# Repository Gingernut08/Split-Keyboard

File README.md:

50 Key Compact Keyboard with 2 function layers and wireless capability

CAD Case Assembled

PCB

Schematic repeated for each half

BOM:

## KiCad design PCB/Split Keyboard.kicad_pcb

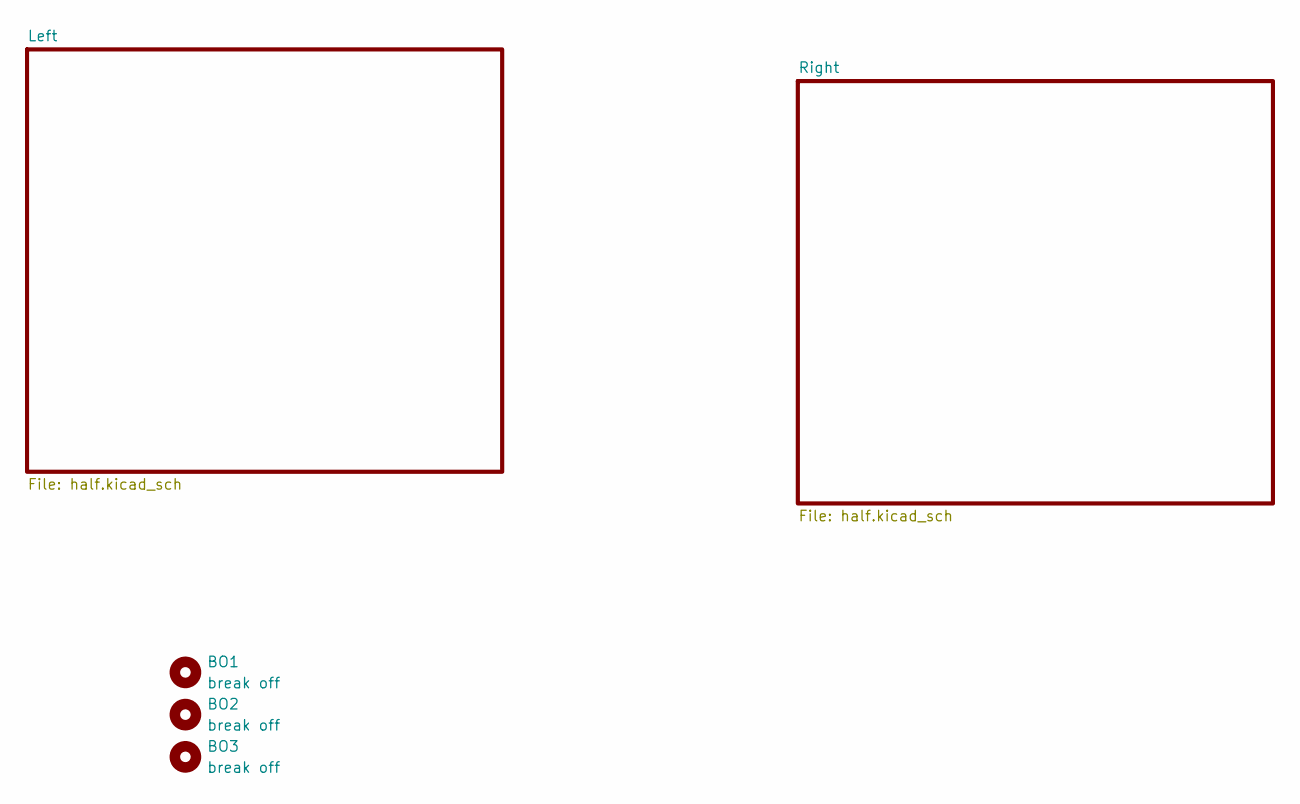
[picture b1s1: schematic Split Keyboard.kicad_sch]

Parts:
BO1, BO2, BO3: break off; mouse-bite-5mm-slot

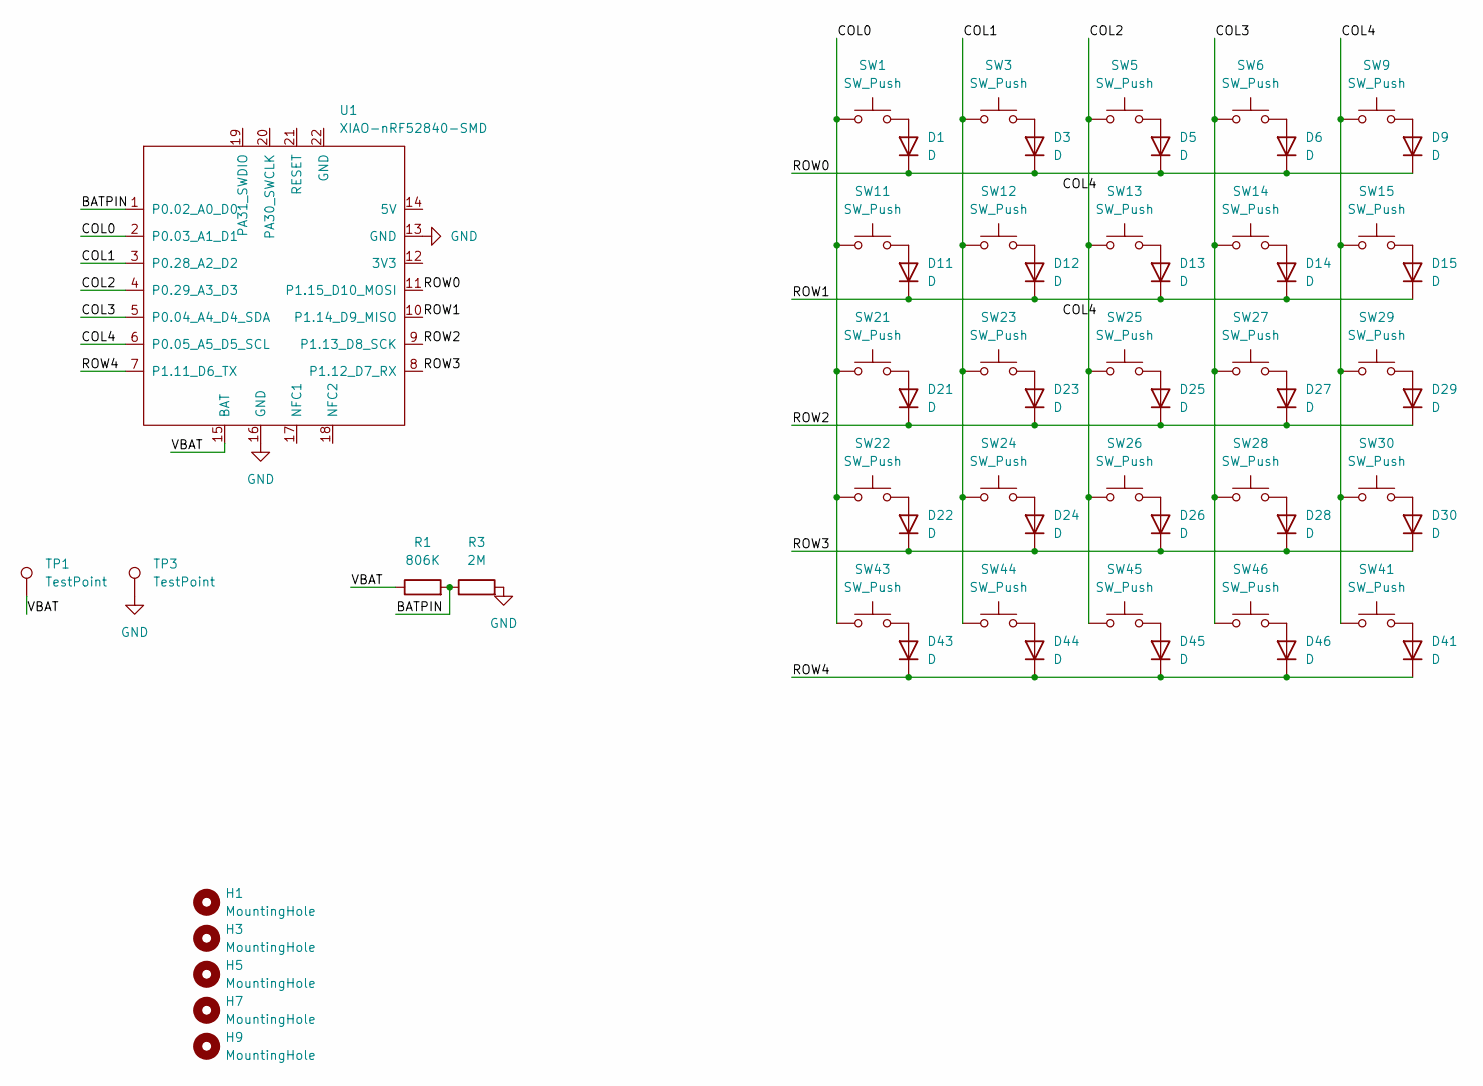
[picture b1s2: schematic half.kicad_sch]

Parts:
D1, D3, D5, D6, D9, D11, D12, D13, D14, D15, D21, D22, D23, D24, D25, D26, D27, D28, D29, D30, D41, D43, D44, D45, D46: D; D_SOD-123
H1, H3, H5, H7, H9: MountingHole; MountingHole_3.2mm_M3
R1: 806K; R_0805_2012Metric
R3: 2M; R_0805_2012Metric
SW1, SW3, SW5, SW6, SW9, SW11, SW12, SW13, SW14, SW15, SW21, SW22, SW23, SW24, SW25, SW26, SW27, SW28, SW29, SW30, SW41, SW43, SW44, SW45, SW46: SW_Push; SW_MX_HS_CPG151101S11_1u
TP1, TP3: TestPoint; TestPoint_Pad_D2.0mm
U1: XIAO-nRF52840-SMD; modified-XIAO-nRF52840-SMD

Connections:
/Right/BATPIN: R1.2, R3.1, U1.1 (P0.02_A0_D0)
/Right/COL0: SW1.1, SW11.1, SW21.1, SW22.1, SW43.1, U1.2 (P0.03_A1_D1)
/Right/COL1: SW3.1, SW12.1, SW23.1, SW24.1, SW44.1, U1.3 (P0.28_A2_D2)
/Right/COL2: SW5.1, SW13.1, SW25.1, SW26.1, SW45.1, U1.4 (P0.29_A3_D3)
/Right/COL3: SW6.1, SW14.1, SW27.1, SW28.1, SW46.1, U1.5 (P0.04_A4_D4_SDA)
/Right/COL4: SW9.1, SW15.1, SW29.1, SW30.1, SW41.1, U1.6 (P0.05_A5_D5_SCL)
/Right/ROW0: D1.1 (K), D3.1 (K), D5.1 (K), D6.1 (K), D9.1 (K), U1.11 (P1.15_D10_MOSI)
/Right/ROW1: D11.1 (K), D12.1 (K), D13.1 (K), D14.1 (K), D15.1 (K), U1.10 (P1.14_D9_MISO)
/Right/ROW2: D21.1 (K), D23.1 (K), D25.1 (K), D27.1 (K), D29.1 (K), U1.9 (P1.13_D8_SCK)
/Right/ROW3: D22.1 (K), D24.1 (K), D26.1 (K), D28.1 (K), D30.1 (K), U1.8 (P1.12_D7_RX)
/Right/ROW4: D41.1 (K), D43.1 (K), D44.1 (K), D45.1 (K), D46.1 (K), U1.7 (P1.11_D6_TX)
/Right/VBAT: R1.1, TP1.1, U1.15 (BAT)
GND: R3.2, TP3.1, U1.13 (GND), U1.16 (GND); also elsewhere on the board
unnamed: D1.2 (A), SW1.2
unnamed: D3.2 (A), SW3.2
unnamed: D5.2 (A), SW5.2
unnamed: D6.2 (A), SW6.2
unnamed: D9.2 (A), SW9.2
unnamed: D11.2 (A), SW11.2
unnamed: D12.2 (A), SW12.2
unnamed: D13.2 (A), SW13.2
unnamed: D14.2 (A), SW14.2
unnamed: D15.2 (A), SW15.2
unnamed: D21.2 (A), SW21.2
unnamed: D22.2 (A), SW22.2
unnamed: D23.2 (A), SW23.2
unnamed: D24.2 (A), SW24.2
unnamed: D25.2 (A), SW25.2
unnamed: D26.2 (A), SW26.2
unnamed: D27.2 (A), SW27.2
unnamed: D28.2 (A), SW28.2
unnamed: D29.2 (A), SW29.2
unnamed: D30.2 (A), SW30.2
unnamed: D41.2 (A), SW41.2
unnamed: D43.2 (A), SW43.2
unnamed: D44.2 (A), SW44.2
unnamed: D45.2 (A), SW45.2
unnamed: D46.2 (A), SW46.2

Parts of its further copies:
D2, D4, D7, D8, D10, D16, D17, D18, D19, D20, D31, D32, D33, D34, D35, D36, D37, D38, D39, D40, D42, D47, D48, D49, D50: D; D_SOD-123
H2, H4, H6, H8, H10: MountingHole; MountingHole_3.2mm_M3
R2: 806K; R_0805_2012Metric
R4: 2M; R_0805_2012Metric
SW2, SW4, SW7, SW8, SW10, SW16, SW17, SW18, SW19, SW20, SW31, SW32, SW33, SW34, SW35, SW36, SW37, SW38, SW39, SW40, SW42, SW47, SW48, SW49, SW50: SW_Push; SW_MX_HS_CPG151101S11_1u
TP2, TP4: TestPoint; TestPoint_Pad_D2.0mm
U2: XIAO-nRF52840-SMD; modified-XIAO-nRF52840-SMD

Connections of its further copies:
/Left/BATPIN: R2.2, R4.1, U2.1 (P0.02_A0_D0)
/Left/COL0: SW2.1, SW16.1, SW31.1, SW32.1, SW47.1, U2.2 (P0.03_A1_D1)
/Left/COL1: SW4.1, SW17.1, SW33.1, SW34.1, SW48.1, U2.3 (P0.28_A2_D2)
/Left/COL2: SW7.1, SW18.1, SW35.1, SW36.1, SW49.1, U2.4 (P0.29_A3_D3)
/Left/COL3: SW8.1, SW19.1, SW37.1, SW38.1, SW50.1, U2.5 (P0.04_A4_D4_SDA)
/Left/COL4: SW10.1, SW20.1, SW39.1, SW40.1, SW42.1, U2.6 (P0.05_A5_D5_SCL)
/Left/ROW0: D2.1 (K), D4.1 (K), D7.1 (K), D8.1 (K), D10.1 (K), U2.11 (P1.15_D10_MOSI)
/Left/ROW1: D16.1 (K), D17.1 (K), D18.1 (K), D19.1 (K), D20.1 (K), U2.10 (P1.14_D9_MISO)
/Left/ROW2: D31.1 (K), D33.1 (K), D35.1 (K), D37.1 (K), D39.1 (K), U2.9 (P1.13_D8_SCK)
/Left/ROW3: D32.1 (K), D34.1 (K), D36.1 (K), D38.1 (K), D40.1 (K), U2.8 (P1.12_D7_RX)
/Left/ROW4: D42.1 (K), D47.1 (K), D48.1 (K), D49.1 (K), D50.1 (K), U2.7 (P1.11_D6_TX)
/Left/VBAT: R2.1, TP2.1, U2.15 (BAT)
GND: R4.2, TP4.1, U2.13 (GND), U2.16 (GND); also elsewhere on the board
unnamed: D2.2 (A), SW2.2
unnamed: D4.2 (A), SW4.2
unnamed: D7.2 (A), SW7.2
unnamed: D8.2 (A), SW8.2
unnamed: D10.2 (A), SW10.2
unnamed: D16.2 (A), SW16.2
unnamed: D17.2 (A), SW17.2
unnamed: D18.2 (A), SW18.2
unnamed: D19.2 (A), SW19.2
unnamed: D20.2 (A), SW20.2
unnamed: D31.2 (A), SW31.2
unnamed: D32.2 (A), SW32.2
unnamed: D33.2 (A), SW33.2
unnamed: D34.2 (A), SW34.2
unnamed: D35.2 (A), SW35.2
unnamed: D36.2 (A), SW36.2
unnamed: D37.2 (A), SW37.2
unnamed: D38.2 (A), SW38.2
unnamed: D39.2 (A), SW39.2
unnamed: D40.2 (A), SW40.2
unnamed: D42.2 (A), SW42.2
unnamed: D47.2 (A), SW47.2
unnamed: D48.2 (A), SW48.2
unnamed: D49.2 (A), SW49.2
unnamed: D50.2 (A), SW50.2

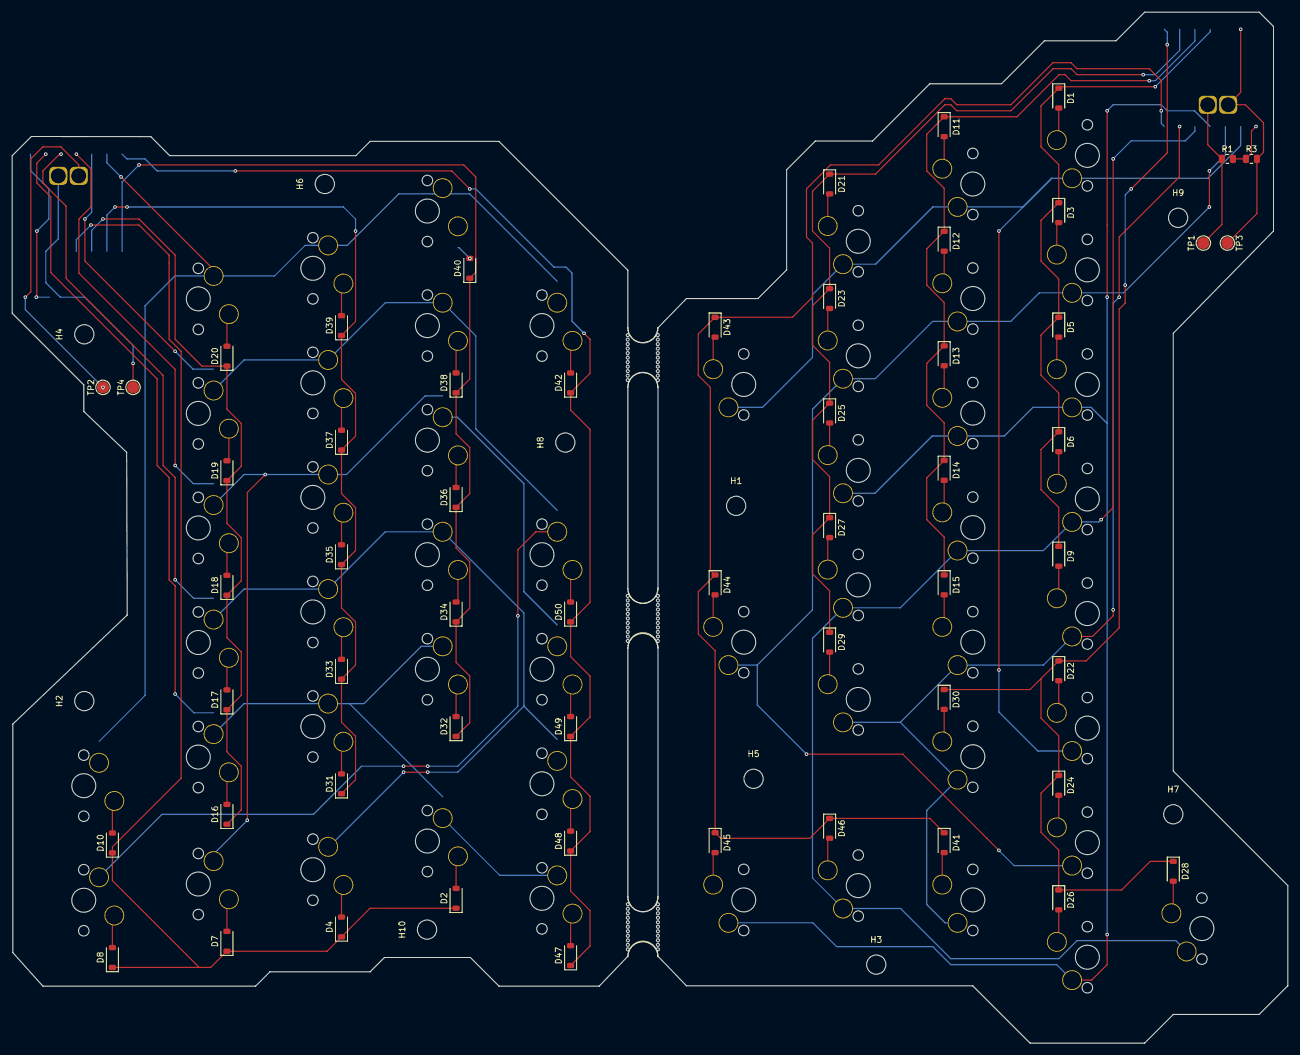
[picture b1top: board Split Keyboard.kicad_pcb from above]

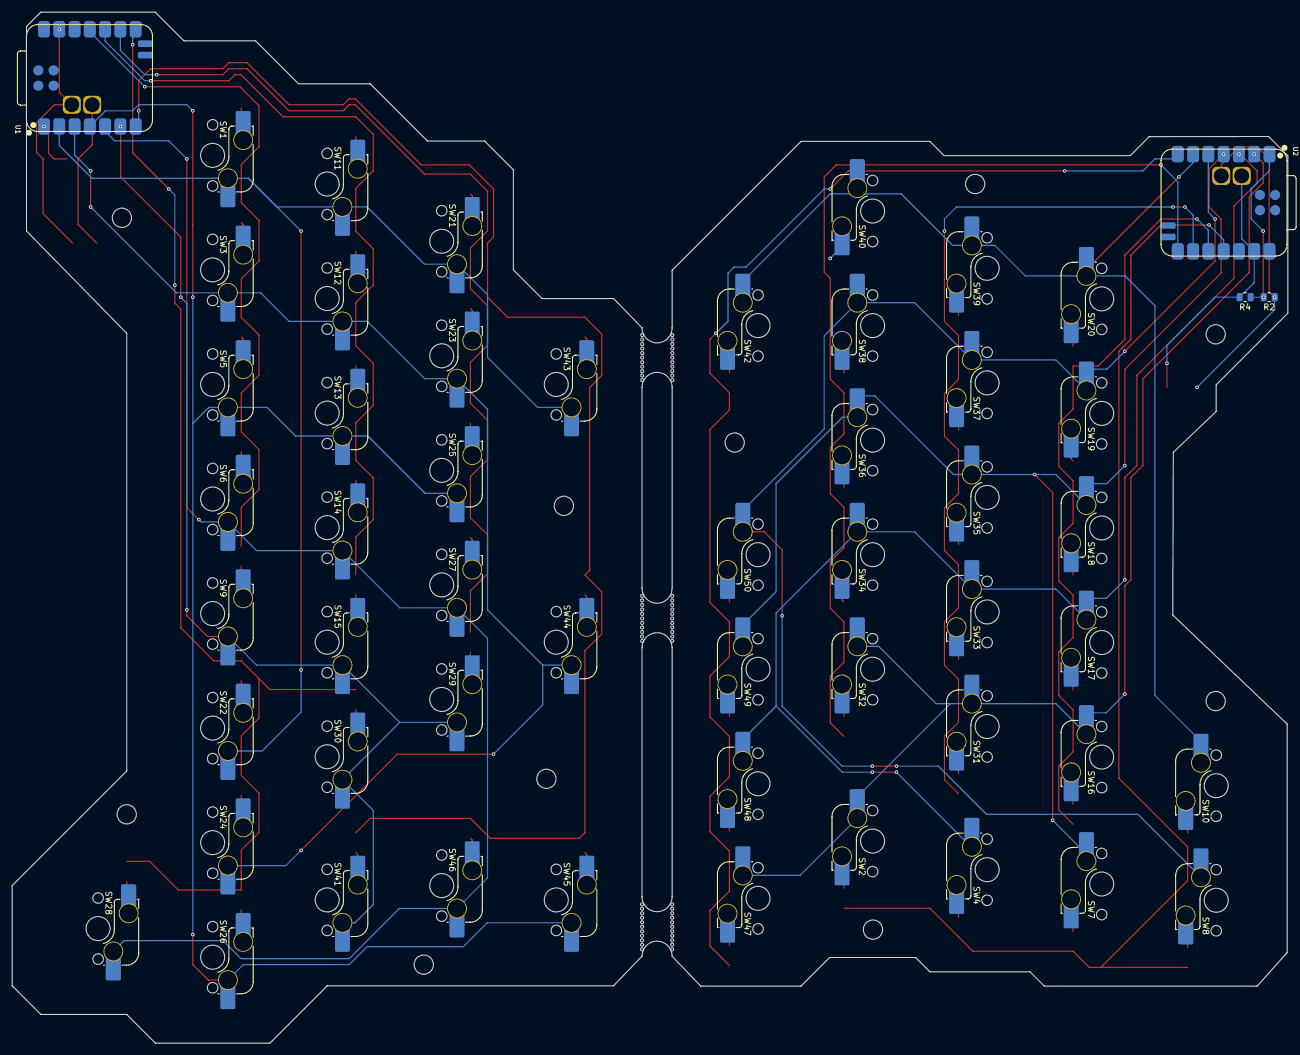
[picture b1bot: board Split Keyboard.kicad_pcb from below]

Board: 2 copper layers, 212.1 x 171.5 mm, 123 parts (54 on the bottom side), 75 nets.

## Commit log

2025-12-19 Add README content for 50 Key Compact Keyboard
    Added detailed information about the 50 Key Compact Keyboard, including images and BOM.
2025-12-19 Enhance README with images and BOM information
    Added images and BOM details to the README.
2026-01-26 Create cadPath
2026-01-26 Add temporary file for filepath
2026-01-26 Rename PCBPath to pcbPath
2026-02-02 Replace images in README with updated versions
    Updated images in the README to reflect new assets.
